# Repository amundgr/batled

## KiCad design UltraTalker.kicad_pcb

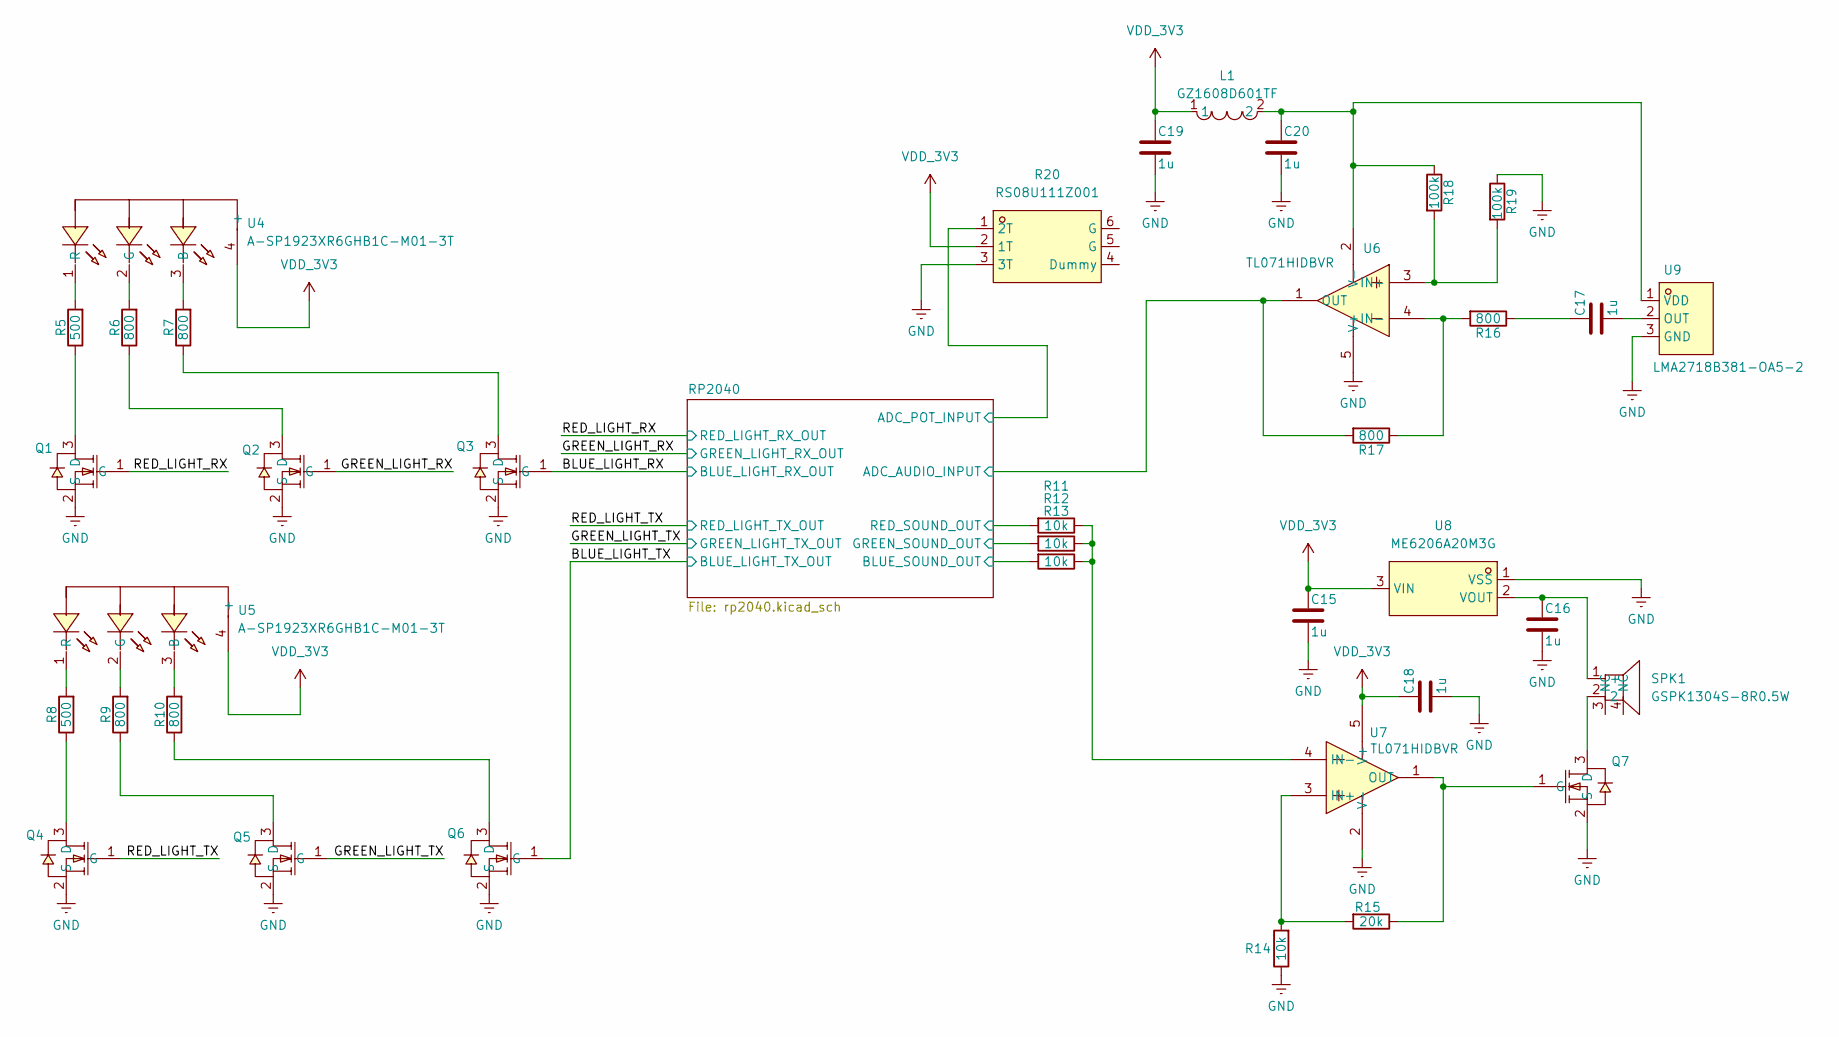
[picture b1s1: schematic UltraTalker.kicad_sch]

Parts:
C15, C16, C17, C18, C19, C20: 1u; C_0603_1608Metric
L1: GZ1608D601TF; L0603; LCSC Part C1002
Q1, Q2, Q3, Q4, Q5, Q6, Q7: BSS138_C112239; SOT-23-3_L2.9-W1.6-P1.90-LS2.8-BR; LCSC Part C112239
R5, R8: 500; R_0603_1608Metric
R6, R7, R9, R10, R16, R17: 800; R_0603_1608Metric
R11, R12, R13, R14: 10k; R_0603_1608Metric
R15: 20k; R_0603_1608Metric
R18, R19: 100k; R_0603_1608Metric
R20: RS08U111Z001; RES-ADJ-SMD_L13.2-W3.0_RS08U111Z001; LCSC Part C202411
SPK1: GSPK1304S-8R0.5W; BUZ-SMD_4P-L13.0-W13.0-P11.4-BL; LCSC Part C2847318
U4, U5: A-SP1923XR6GHB1C-M01-3T; LED-SMD_4P-L1.6-W1.5-BL-1; LCSC Part C19171339
U6, U7: TL071HIDBVR; SOT-23-5_L2.9-W1.5-P0.95-LS2.8-BL; LCSC Part C4370629
U8: ME6206A20M3G; SOT-23-3_L3.0-W1.7-P0.95-LS2.9-BR; LCSC Part C128056
U9: LMA2718B381-OA5-2; MIC-SMD_3P-L2.8-W1.9_ZTS6056; LCSC Part C7587902

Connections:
/BLUE_LIGHT_RX: Q3.1 (G); also elsewhere on the board
/BLUE_LIGHT_TX: Q6.1 (G); also elsewhere on the board
/GREEN_LIGHT_RX: Q2.1 (G); also elsewhere on the board
/GREEN_LIGHT_TX: Q5.1 (G); also elsewhere on the board
/RED_LIGHT_RX: Q1.1 (G); also elsewhere on the board
/RED_LIGHT_TX: Q4.1 (G); also elsewhere on the board
/RP2040/ADC_AUDIO_INPUT: R17.2, U6.1 (OUT); also elsewhere on the board
/RP2040/ADC_POT_INPUT: R20.1 (2T); also elsewhere on the board
/RP2040/BLUE_SOUND_OUT: R13.2; also elsewhere on the board
/RP2040/GREEN_SOUND_OUT: R12.2; also elsewhere on the board
/RP2040/RED_SOUND_OUT: R11.2; also elsewhere on the board
GND: C15.2, C16.2, C18.2, C19.2, C20.2, Q1.2 (S), Q2.2 (S), Q3.2 (S), Q4.2 (S), Q5.2 (S), Q6.2 (S), Q7.2 (S), R14.1, R19.1, R20.3 (3T), U6.5 (V+), U7.2 (V-), U8.1 (VSS), U9.3 (GND); also elsewhere on the board
unnamed: C17.1, R16.1
unnamed: Q1.3 (D), R5.1
unnamed: Q2.3 (D), R6.1
unnamed: Q3.3 (D), R7.1
unnamed: Q4.3 (D), R8.1
unnamed: Q5.3 (D), R9.1
unnamed: Q6.3 (D), R10.1
unnamed: Q7.3 (D), SPK1.2
unnamed: Q7.1 (G), R15.1, U7.1 (OUT)
unnamed: C16.1, SPK1.1 (+), U8.2 (VOUT)
unnamed: R7.2, U4.3 (B)
unnamed: R6.2, U4.2 (G)
unnamed: R5.2, U4.1 (R)
unnamed: R10.2, U5.3 (B)
unnamed: R9.2, U5.2 (G)
unnamed: R8.2, U5.1 (R)
unnamed: R18.2, R19.2, U6.3 (IN+)
unnamed: R16.2, R17.1, U6.4 (IN-)
unnamed: C20.1, L1.2, R18.1, U6.2 (V-), U9.1 (VDD)
unnamed: R14.2, R15.2, U7.3 (IN+)
unnamed: R11.1, R12.1, R13.1, U7.4 (IN-)
unnamed: C17.2, U9.2 (OUT)
VDD_3V3: C15.1, C18.1, C19.1, L1.1, R20.2 (1T), U4.4 (+), U5.4 (+), U7.5 (V+), U8.3 (VIN); also elsewhere on the board

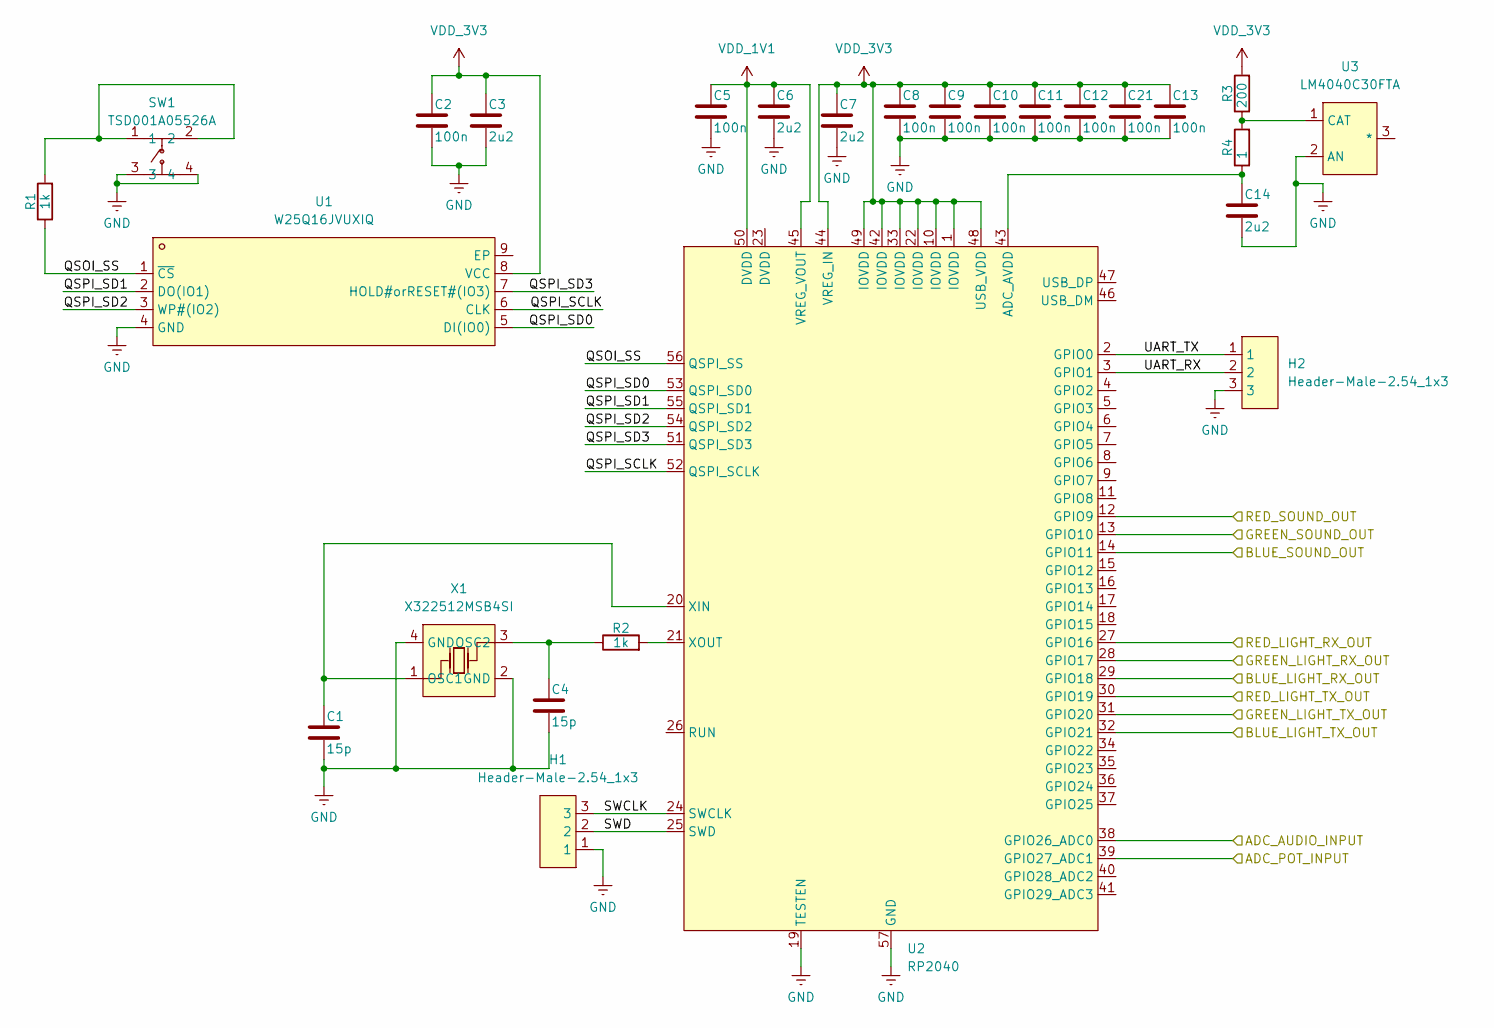
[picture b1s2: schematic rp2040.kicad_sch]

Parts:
C1, C4: 15p; C_0603_1608Metric
C2, C5, C8, C9, C10, C11, C12, C13, C21: 100n; C_0603_1608Metric
C3, C6, C7, C14: 2u2; C_0603_1608Metric
H1, H2: Header-Male-2.54_1x3; HDR-TH_3P-P2.54-V-M-1; LCSC Part C49257
R1, R2: 1k; R_0603_1608Metric
R3: 200; R_0603_1608Metric
R4: 1; R_0603_1608Metric
SW1: TSD001A05526A; SW-TH_4P-L6.0-W6.0-P4.50-LS6.3; LCSC Part C2888546
U1: W25Q16JVUXIQ; USON-8_L3.0-W2.0-P0.50-BL-EP; LCSC Part C2843335
U2: RP2040; LQFN-56_L7.0-W7.0-P0.4-EP; LCSC Part C2040
U3: LM4040C30FTA; SOT-23-3_L2.9-W1.3-P1.90-LS2.4-BR; LCSC Part C460608
X1: X322512MSB4SI; CRYSTAL-SMD_4P-L3.2-W2.5-BL; LCSC Part C9002

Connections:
/BLUE_LIGHT_RX: U2.29 (GPIO18); also elsewhere on the board
/BLUE_LIGHT_TX: U2.32 (GPIO21); also elsewhere on the board
/GREEN_LIGHT_RX: U2.28 (GPIO17); also elsewhere on the board
/GREEN_LIGHT_TX: U2.31 (GPIO20); also elsewhere on the board
/RED_LIGHT_RX: U2.27 (GPIO16); also elsewhere on the board
/RED_LIGHT_TX: U2.30 (GPIO19); also elsewhere on the board
/RP2040/ADC_AUDIO_INPUT: U2.38 (GPIO26_ADC0); also elsewhere on the board
/RP2040/ADC_POT_INPUT: U2.39 (GPIO27_ADC1); also elsewhere on the board
/RP2040/BLUE_SOUND_OUT: U2.14 (GPIO11); also elsewhere on the board
/RP2040/GREEN_SOUND_OUT: U2.13 (GPIO10); also elsewhere on the board
/RP2040/QSOI_SS: R1.1, U1.1 (~CS), U2.56 (QSPI_SS)
/RP2040/QSPI_SCLK: U1.6 (CLK), U2.52 (QSPI_SCLK)
/RP2040/QSPI_SD0: U1.5 (DI(IO0)), U2.53 (QSPI_SD0)
/RP2040/QSPI_SD1: U1.2 (DO(IO1)), U2.55 (QSPI_SD1)
/RP2040/QSPI_SD2: U1.3 (WP#(IO2)), U2.54 (QSPI_SD2)
/RP2040/QSPI_SD3: U1.7 (HOLD#orRESET#(IO3)), U2.51 (QSPI_SD3)
/RP2040/RED_SOUND_OUT: U2.12 (GPIO9); also elsewhere on the board
/RP2040/SWCLK: H1.3, U2.24 (SWCLK)
/RP2040/SWD: H1.2, U2.25 (SWD)
/RP2040/UART_RX: H2.2, U2.3 (GPIO1)
/RP2040/UART_TX: H2.1, U2.2 (GPIO0)
GND: C1.2, C2.2, C3.2, C4.2, C5.2, C6.2, C7.2, C8.2, C9.2, C10.2, C11.2, C12.2, C13.2, C14.2, C21.2, H1.1, H2.3, SW1.3, SW1.4, U1.4 (GND), U2.19 (TESTEN), U2.57 (GND), U3.2 (AN), X1.2 (GND), X1.4 (GND); also elsewhere on the board
unnamed: R1.2, SW1.1, SW1.2
unnamed: C14.1, R4.1, U2.43 (ADC_AVDD)
unnamed: C1.1, U2.20 (XIN), X1.1 (OSC1)
unnamed: R2.2, U2.21 (XOUT)
unnamed: R3.1, R4.2, U3.1 (CAT)
unnamed: C4.1, R2.1, X1.3 (OSC2)
VDD_1V1: C5.1, C6.1, U2.45 (VREG_VOUT), U2.50 (DVDD)
VDD_3V3: C2.1, C3.1, C7.1, C8.1, C9.1, C10.1, C11.1, C12.1, C13.1, C21.1, R3.2, U1.8 (VCC), U2.1 (IOVDD), U2.10 (IOVDD), U2.22 (IOVDD), U2.33 (IOVDD), U2.42 (IOVDD), U2.44 (VREG_IN), U2.48 (USB_VDD), U2.49 (IOVDD); also elsewhere on the board

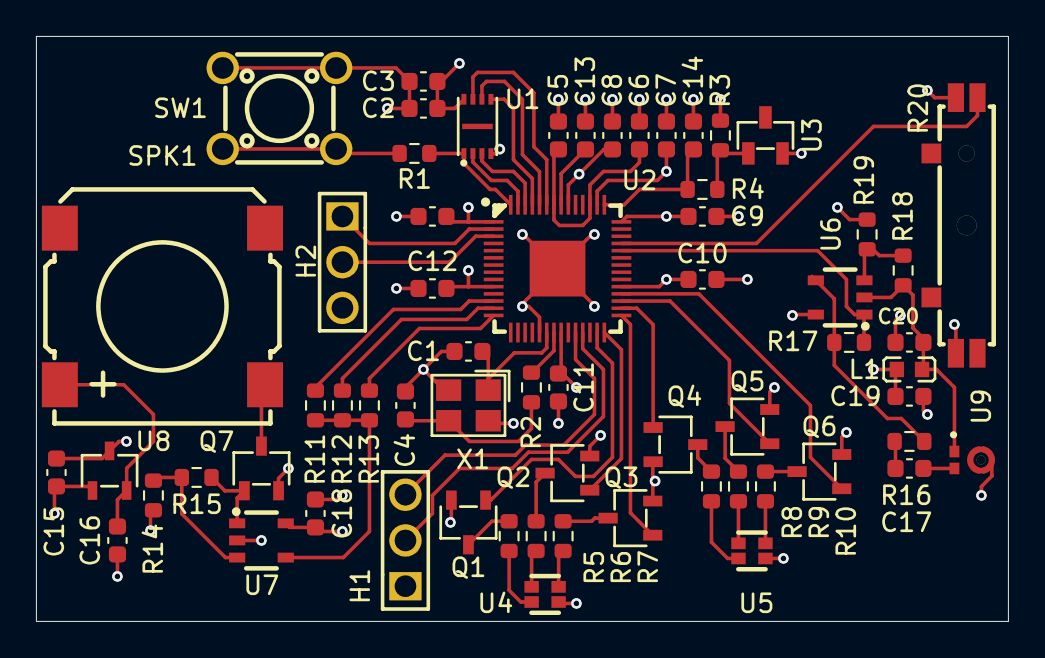
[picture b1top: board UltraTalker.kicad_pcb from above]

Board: 4 copper layers, 54.0 x 32.5 mm, 63 parts (0 on the bottom side), 52 nets.

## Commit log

2025-02-03 initial commit (hihi)
